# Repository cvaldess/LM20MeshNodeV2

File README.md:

# LM20MeshNode

Pocket [Meshtastic](https://meshtastic.org/) node built around the Nordic **nRF54LM20A**
(Minew ME54BS13 module), with a Minew **MS21SF1** (SX1262) LoRa module, a Minew **ME31GR02**
GNSS receiver and a Nordic **nPM1300** PMIC for a single-cell LiPo battery. It connects to the
phone over Bluetooth LE.

| Front | Back |
|-------|------|
|  |  |

> **Status:** revision 0.2, not yet manufactured or tested. It replaces the Ebyte modules of
> revision 0.1 (E22-900MM22S and E108-GN04S) with Minew modules and adds a backup cell for the
> GNSS. Revision 0.1 is in the [LM20MeshNode](https://github.com/cvaldess/LM20MeshNode)
> repository. A Meshtastic firmware
> variant for revision 0.1 is under review as a draft: see [Meshtastic firmware](#meshtastic-firmware).

## Features

- **MCU:** Minew [nRF54LM20A-ME54BS13](https://en.minewsemi.com/bluetooth-module/nrf54lm20a-me54bs13) (nRF54LM20A, Bluetooth LE with integrated antenna), USB-C to the
  nRF54LM20A USB port, 2×5 1.27 mm Cortex Debug (SWD) header (J201) and debug UART pads.
- **LoRa:** Minew [MS21SF1-SX1262](https://en.minewsemi.com/lora-module/llcc68-sx1262-me21ls1a) (SX1262, up to 22 dBm). The antenna goes to the U.FL
  connector on the module itself. The RF switch inside the module is driven by DIO2, so the
  MCU drives no RXEN/TXEN line. The module supply has its own filter footprint: FB301 (0 Ω,
  or a ferrite bead) and C303.
- **GNSS:** Minew [ME31GR02](https://en.minewsemi.com/gnss-module/me31gr02) (Beken BK166X chip) with U.FL antenna connector (J401). L401 (47 nH)
  feeds an active antenna from the module's VCC_RF output; a passive antenna also works if it
  is not a DC short. The GNSS supply (nPM1300 BUCK1) is off at power-up and is switched by
  firmware.
- **GNSS backup:** a rechargeable Seiko MS621FE coin cell (BT401) on V_BCKP, charged from
  3.3 V through a BAT54WS diode and 1 kΩ. It keeps the RTC and ephemeris data while the board
  is off, for faster fixes.
- **Power:** nPM1300 PMIC with USB-C input and ESD protection, 1S LiPo charger (JST PH 2.0,
  J102), on-board 10 kΩ NTC, 3.3 V main rail (BUCK2), power button (SW101) on SHPHLD, charge
  and error LEDs, and a battery voltage divider to an ADC input.
- **User interface:** 0.91" 128×32 OLED (SSD1306) on the back, three side buttons (UP, OK,
  DOWN), magnetic buzzer and a status LED.
- **Sensors:** Nyfea SHT41-P-NF temperature/humidity sensor (SHT41 compatible), thermally
  isolated by a slot, and an ST LSM6DS3TR-C IMU wired for wake-on-motion (INT1 on P0.02).
- **Expansion:** 4-pin 1 mm I²C connector (J501, Qwiic-style pinout: GND, 3.3 V, SDA, SCL).
- **Board:** 4 layers (signal / GND / 3.3 V / signal), 40 × 85.68 mm, 1.6 mm, M2 mounting
  holes. All SMD parts are on the top side.

## nRF54LM20A pin map

| Function | Pin | Notes |
|----------|-----|-------|
| LoRa SPI (SPIM22): SCK, MOSI, MISO, NSS | P1.17, P1.16, P1.15, P1.18 | |
| LoRa BUSY, DIO1, NRST | P1.19, P1.23, P1.26 | RF switch driven by DIO2 inside the module |
| I²C (TWIM30): SDA, SCL | P0.03, P0.04 | 4.7 kΩ pull-ups |
| GNSS UART (UARTE20): MCU TX → GNSS RXD, GNSS TXD → MCU RX | P1.03, P1.29 | 1 kΩ series resistors; test pads TP402 (GNSS RXD) and TP401 (GNSS TXD) |
| GNSS PPS | P1.04 | |
| GNSS reset | P1.00 | Only through R405 (0 Ω, not fitted). The ME31GR02 reset has an internal pull-up |
| GNSS power enable | P1.05 | To nPM1300 GPIO0 |
| PMIC interrupt | P1.06 | From nPM1300 GPIO1 |
| Battery voltage (divider 2 × 1 MΩ) | P1.30 (AIN2) | |
| Buttons UP, OK, DOWN | P1.27, P1.28, P1.25 | |
| Buzzer (PWM) | P1.09 | |
| Status LED | P2.00 | |
| IMU INT1, INT2 | P0.02, P0.05 | P0 can wake the chip from System OFF |
| Debug UART (UARTE00): TX, RX | P2.02, P2.07 | Test pads |

P1.12 and P1.13 (LoRa TXEN and RXEN in revision 0.1) are free.

I²C devices: nPM1300 `0x6B`, LSM6DS3TR-C `0x6A`, SHT41 `0x44`, OLED `0x3C`.

### Firmware notes

- The nPM1300 starts with the **battery charger disabled**. Firmware must enable charging
  over I²C. The board is designed so that LoRa and Bluetooth work without a PMIC driver.
- The MS21SF1 has a crystal, not a TCXO: do not define a DIO3 TCXO voltage. Use DIO2 as the RF
  switch and define no RXEN/TXEN pins.
- The GNSS rail (BUCK1) must be set to 3.3 V and enabled by firmware.
- The ME31GR02 uses a Beken BK166X chip, which Meshtastic does not detect yet. It talks NMEA at
  115200 bps by default, prints `$POLRS` or `$BKCHIP` at start-up and is configured with
  `$POLCFG…` commands.
- While the GNSS is unpowered or running from the backup cell, no MCU pin connected to it may
  be driven high: put the UART TX pin in input mode with a pull-down. This is why R405 (reset)
  is not fitted.

## Meshtastic firmware

The `lm20meshnode` variant is under review upstream. It was written for **revision 0.1**
(Ebyte modules). All three pull requests are open, and nothing has run on hardware yet:

| Part | Pull request |
|------|--------------|
| Meshtastic variant (draft, on top of the nRF54LM20-DK support in [#12130](https://github.com/meshtastic/firmware/pull/12130)) | [meshtastic/firmware#12354](https://github.com/meshtastic/firmware/pull/12354) |
| Arduino core variant | [andyshinn/nRF54_Arduino#3](https://github.com/andyshinn/nRF54_Arduino/pull/3) |
| Bootloader board | [andyshinn/nRF54_Bootloader#3](https://github.com/andyshinn/nRF54_Bootloader/pull/3) |

Until they are merged, the variant builds from the `feat/lm20meshnode-variant` branch of
[cvaldess/firmware](https://github.com/cvaldess/firmware/tree/feat/lm20meshnode-variant) with
`pio run -e lm20meshnode`. The core and the bootloader come from forks (the core at a pinned commit,
the bootloader at the tag `v0.5.0-lm20meshnode.1`).

What the variant does on revision 0.1:

- **nPM1300**, set up over I²C at boot: BUCK1 (GNSS rail) at 3.3 V, switched by the PMIC's GPIO0,
  which the GPS code drives from P1.05; battery charger on at 200 mA (`NPM1300_CHARGE_CURRENT_MA`),
  4.20 V (4.00 V in the warm region), with the on-board 10 kΩ NTC; USB input limit 500 mA. BUCK2,
  the 3.3 V main rail, is left on its VSET2 setting. After USB is unplugged and plugged in again,
  the PMIC goes back to its 100 mA startup input limit until the next boot.
- **LoRa** with RXEN from the MCU and TXEN from DIO2, no TCXO. **GNSS** on `Serial1` at 38400 bps.
- **Buttons:** UP, DOWN and OK navigate the screen (up/down input driver). **OLED** at 128×32,
  **buzzer**, **status LED**, **battery** level from AIN2, and the SHT41 and LSM6DS3TR-C drivers.
- **USB-C:** console and Meshtastic API over USB CDC; firmware updates over USB (serial DFU or a
  UF2 drive) or over Bluetooth.
- **Bootloader** (64 KB, application at `0x10000`): hold **OK** at reset for USB DFU (UF2 drive
  `LM20MN-BOOT`), **OK + DOWN** for Bluetooth OTA. The status LED shows the bootloader state.

Revision 0.2 needs these changes in the variant: DIO2 as the RF switch and no RXEN pin (LoRa),
a detection probe for the Beken GNSS at 115200 bps, the GNSS UART TX pin left as an input with a
pull-down while the GNSS is off, and no GNSS reset pin.

Not tested yet, besides the board itself: the nPM1300 setup, GPS on the nRF54 platform (no other
nRF54 variant uses it so far), the 128×32 screen layout and the battery reading through the
2 × 1 MΩ divider.

## Manufacturing

The [`fab/pcbway/`](fab/pcbway/) folder contains:

- `nrflm20-meshnode_rev0.2_pcbway.zip`: Gerber files (4 copper layers, masks, top paste,
  silkscreen, outline), Excellon drill files (PTH and NPTH) and an IPC-D-356 netlist.
- `gerber/`: the same files unzipped, plus drill maps and the drill report.
- `nrflm20-meshnode-BOM-PCBWay.csv`: bill of materials (40 lines, 70 parts) with manufacturer part
  numbers and LCSC codes. A few passives are generic parts, listed by specification.
- `nrflm20-meshnode-CPL-PCBWay.csv`: component placement (centroid) file in millimetres, in the
  same coordinate system as the Gerber files. The OLED (DS501) is the only part on the bottom side.
- `pedido_pcbway.txt`: order settings and pre-production checks (in Spanish).

Not fitted (DNP) and left out of the BOM and placement files: R404, R405. Mounting holes and
test points are not parts and are left out too.

**BT401 is soldered by hand.** The MS621FE-FL11E coin cell must not go through reflow (Seiko:
soldering iron, 5 s maximum, cell below 85 °C), so it is left out of the BOM and placement
files. Its pads do get paste in the stencil, which tins them during reflow; solder the cell
last.

Board: 4 layers, 1.6 mm, 1 oz copper, ENIG recommended, minimum track/space 0.2 mm, minimum
drill 0.3 mm. Stencil: top side only, 0.10 mm, needed by the 0.5 mm pitch parts. Minew
recommends thicker paste on its modules (0.13–0.2 mm); with 0.10 mm, check the castellated
pads after reflow and touch them up with a soldering iron if needed. The standard PCBWay
4-layer stackup is fine; impedance control is not needed (the only RF track on the board, from
J401 to the GNSS module, is 3.9 mm long).

The files are generated from the saved board with `docs/gen/fab_pcbway.py` (Gerber, drill,
IPC-D-356) and `docs/gen/bom_cpl_pcbway.py` (BOM and placement), using KiCad's Python.

## Design files

- [KiCad 10](https://www.kicad.org/) project: `nrflm20-meshnode.kicad_pro`. The root schematic
  has five sheets: power, MCU, LoRa, GNSS and interface.
- `libs/`: project symbols, footprints and 3D models. The MS21SF1 and ME31GR02 footprints were
  converted from Minew's design files (`docs/gen/huellas_minew.py`). The ME54BS13 3D model was
  drawn from its datasheet (`docs/gen/modelo3d_me54bs13.py`).
- **3D models of the MS21SF1 and ME31GR02 are not included yet**: they are Minew's files and are
  waiting for Minew's permission to publish them. The footprints already point to
  `libs/meshnode.3dshapes/MS21SF1_PCB_V1.0.step` and `libs/meshnode.3dshapes/GNSS_MODULE_1010.step`,
  so a clone of this repository renders the board without those two modules.
- `docs/`: block diagram and schematic drafts (SVG). `docs/gen/` has the Python scripts used
  during the design.
- `lista_compra.txt`: shopping list (in Spanish).

Some footprints and 3D models come from [easyeda2kicad](https://github.com/uPesy/easyeda2kicad.py)
(`${EASYEDA2KICAD}`). The footprints are stored in the board file, but their 3D models are
not included in this repository.

## Credits

- **Designed by:** solutions@cvaldess.com
- **Made with:** [Claude Code](https://claude.com/claude-code), [KiCad](https://www.kicad.org/)
  and [Konnect-EDA](https://github.com/Orchis-ai-LLC/Konnect-EDA)
- **Sponsors:** [PCBWay](https://www.pcbway.com/) and [MinewSemi](https://www.minewsemi.com/)
  (ME54BS13, MS21SF1 and ME31GR02 modules)

## License

Copyright © 2026 CValdesS.

This source describes Open Hardware and is licensed under the CERN-OHL-S v2
([LICENSE](LICENSE)). You may redistribute and modify this source and make products using it
under the terms of the CERN-OHL-S v2. This source is distributed WITHOUT ANY EXPRESS OR IMPLIED
WARRANTY, INCLUDING OF MERCHANTABILITY, SATISFACTORY QUALITY AND FITNESS FOR A PARTICULAR
PURPOSE. Please see the CERN-OHL-S v2 for applicable conditions.

Source location: https://github.com/cvaldess/LM20MeshNodeV2

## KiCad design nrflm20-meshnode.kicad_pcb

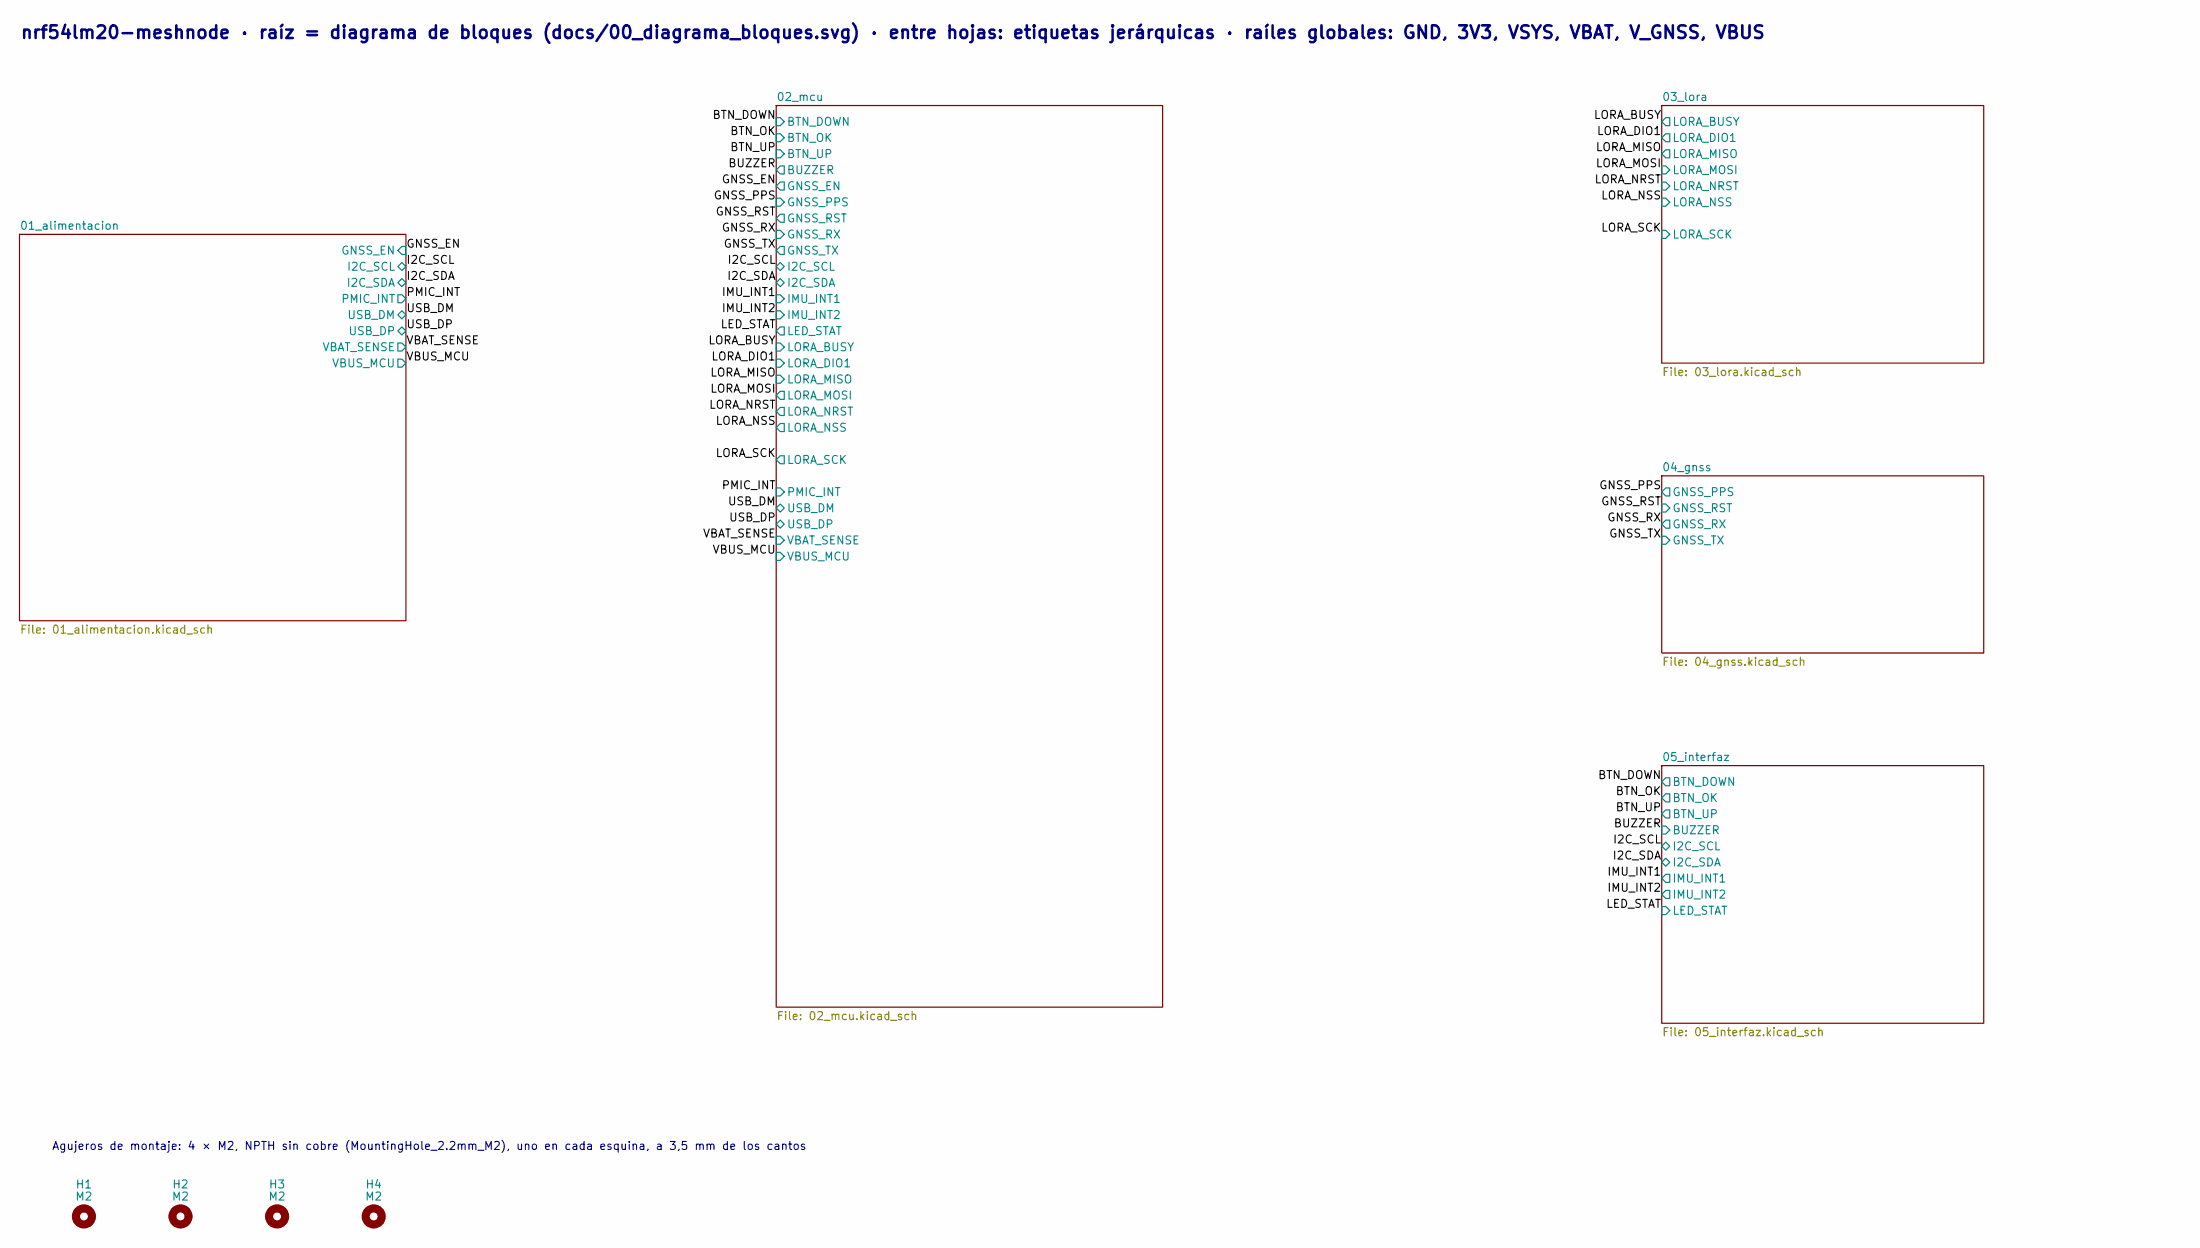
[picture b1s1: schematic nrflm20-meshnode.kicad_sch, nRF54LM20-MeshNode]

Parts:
H1, H2, H3, H4: M2; MountingHole_2.2mm_M2

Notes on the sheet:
nrf54lm20-meshnode · raíz = diagrama de bloques (docs/00_diagrama_bloques.svg) · entre hojas: etiquetas jerárquicas · raíles globales: GND, 3V3, VSYS, VBAT, V_GNSS, VBUS
Agujeros de montaje: 4 × M2, NPTH sin cobre (MountingHole_2.2mm_M2), uno en cada esquina, a 3,5 mm de los cantos

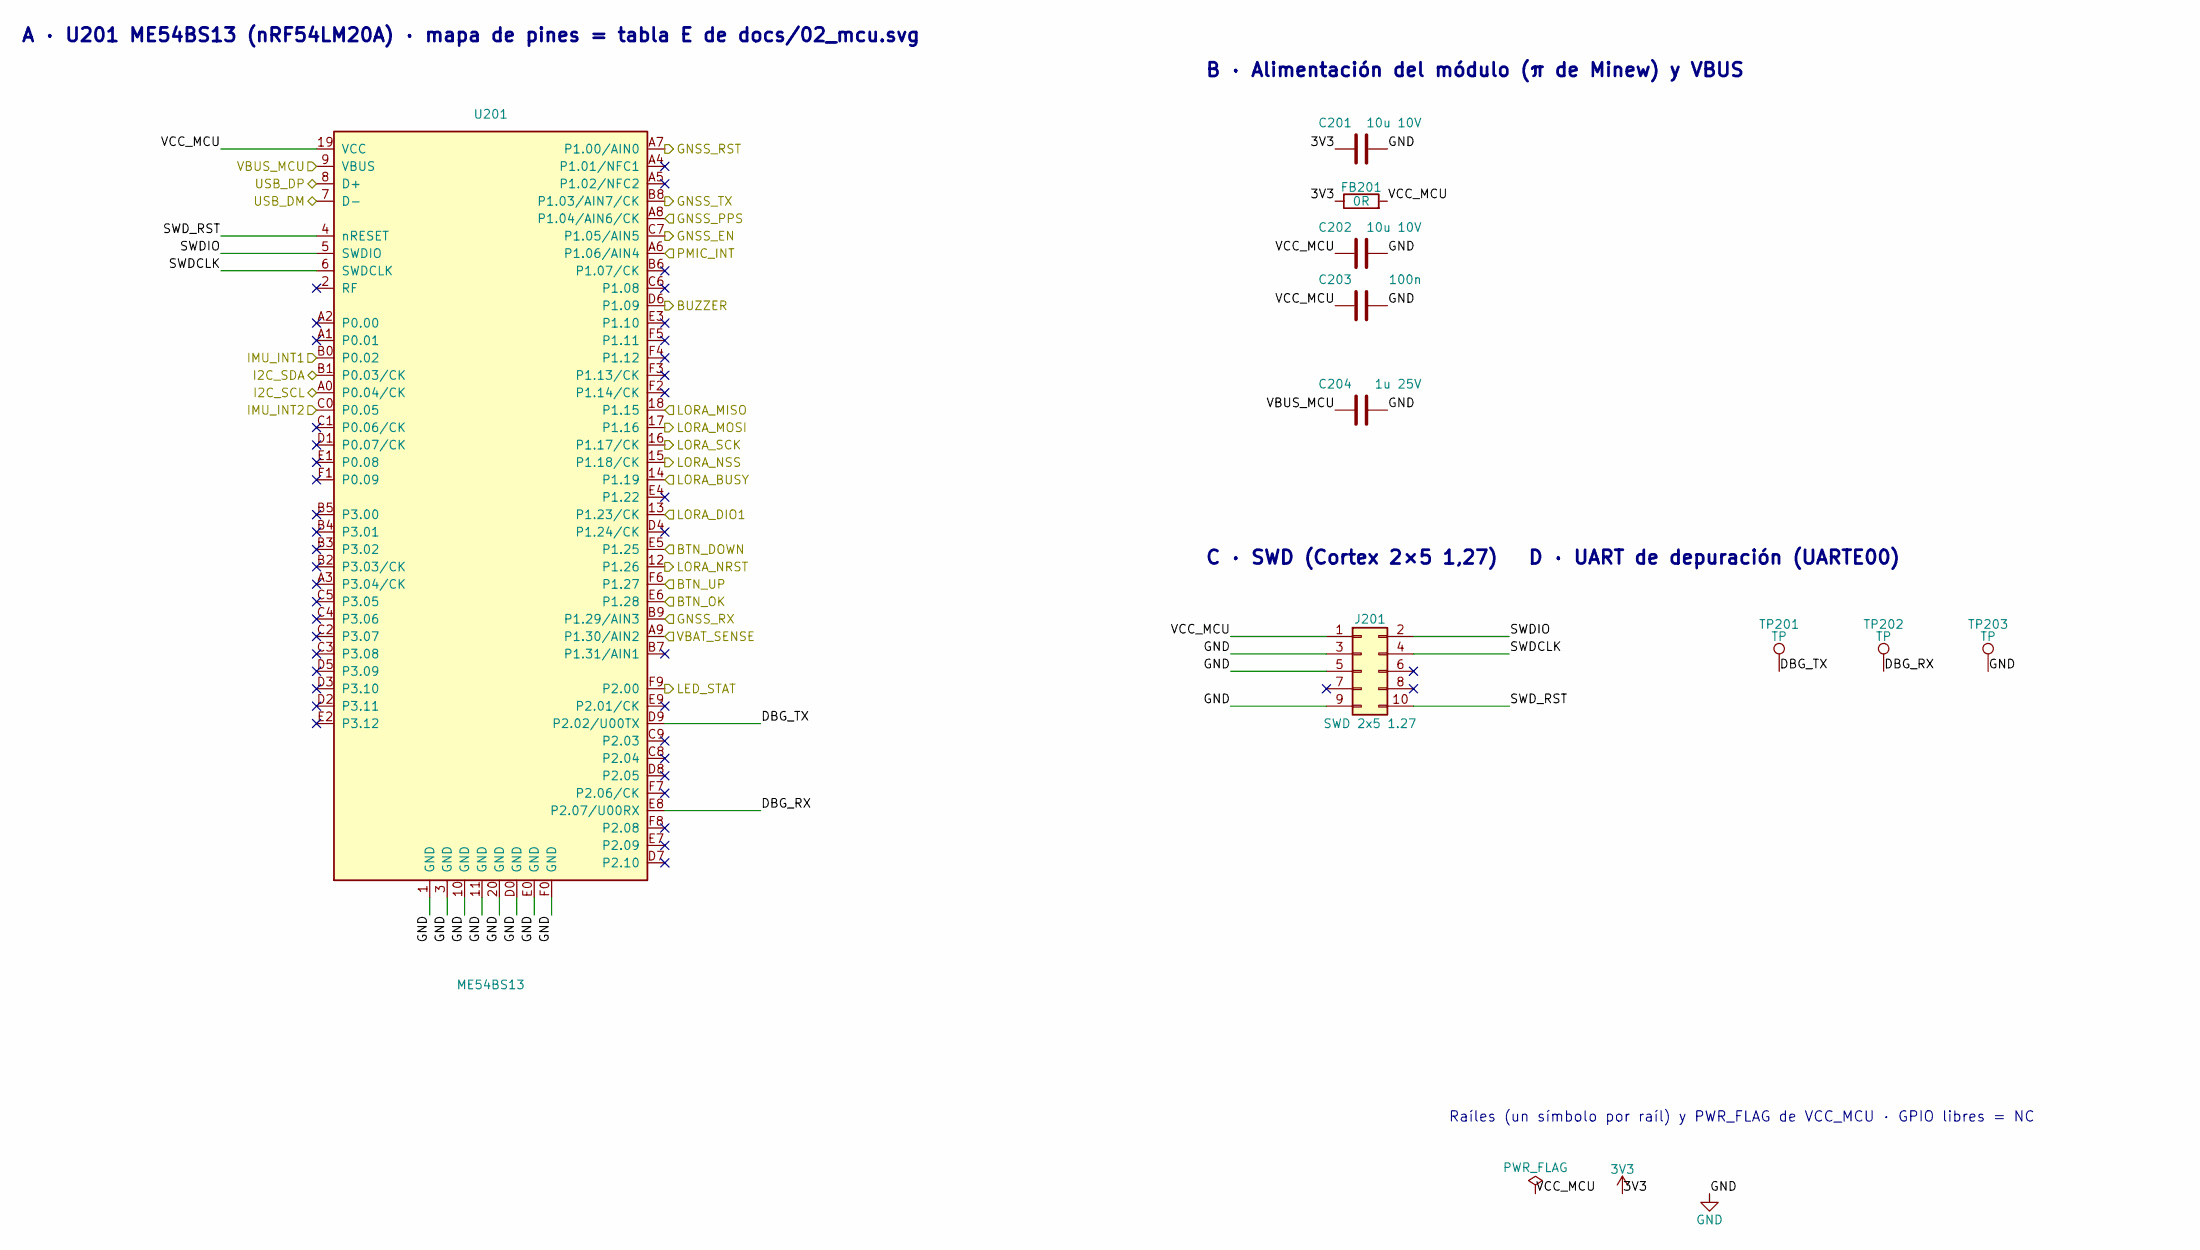
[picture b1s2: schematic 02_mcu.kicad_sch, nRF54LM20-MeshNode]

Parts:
C201, C202: 10u 10V; C_0603_1608Metric
C203: 100n; C_0402_1005Metric; MPN CL05B104KO5NNNC; LCSC Part C1525
C204: 1u 25V; C_0402_1005Metric; MPN CL05A105KA5NQNC; LCSC Part C52923
FB201: 0R; R_0603_1608Metric
J201: SWD 2x5 1.27; PinHeader_2x05_P1.27mm_Vertical_SMD; MPN HX PZ1.27-2x5P TP; LCSC Part C41376037
TP201, TP202, TP203: TP; TestPoint_Pad_D1.0mm
U201: ME54BS13; MPN ME54BS13 (nRF54LM20A)

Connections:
3V3: C201.1, FB201.1; also elsewhere on the board
/02_mcu/DBG_RX: TP202.1 (1_1), U201.E8 (P2.07/U00RX)
/02_mcu/DBG_TX: TP201.1 (1_1), U201.D9 (P2.02/U00TX)
/02_mcu/SWDCLK: J201.4, U201.6 (SWDCLK)
/02_mcu/SWDIO: J201.2, U201.5 (SWDIO)
/02_mcu/SWD_RST: J201.10, U201.4 (nRESET)
/02_mcu/VCC_MCU: C202.1, C203.1, FB201.2, J201.1, U201.19 (VCC)
/BTN_DOWN: U201.E5 (P1.25); also elsewhere on the board
/BTN_OK: U201.E6 (P1.28); also elsewhere on the board
/BTN_UP: U201.F6 (P1.27); also elsewhere on the board
/BUZZER: U201.D6 (P1.09); also elsewhere on the board
/GNSS_EN: U201.C7 (P1.05/AIN5); also elsewhere on the board
/GNSS_PPS: U201.A8 (P1.04/AIN6/CK); also elsewhere on the board
/GNSS_RST: U201.A7 (P1.00/AIN0); also elsewhere on the board
/GNSS_RX: U201.B9 (P1.29/AIN3); also elsewhere on the board
/GNSS_TX: U201.B8 (P1.03/AIN7/CK); also elsewhere on the board
/I2C_SCL: U201.A0 (P0.04/CK); also elsewhere on the board
/I2C_SDA: U201.B1 (P0.03/CK); also elsewhere on the board
/IMU_INT1: U201.B0 (P0.02); also elsewhere on the board
/IMU_INT2: U201.C0 (P0.05); also elsewhere on the board
/LED_STAT: U201.F9 (P2.00); also elsewhere on the board
/LORA_BUSY: U201.14 (P1.19); also elsewhere on the board
/LORA_DIO1: U201.13 (P1.23/CK); also elsewhere on the board
/LORA_MISO: U201.18 (P1.15); also elsewhere on the board
/LORA_MOSI: U201.17 (P1.16); also elsewhere on the board
/LORA_NRST: U201.12 (P1.26); also elsewhere on the board
/LORA_NSS: U201.15 (P1.18/CK); also elsewhere on the board
/LORA_SCK: U201.16 (P1.17/CK); also elsewhere on the board
/PMIC_INT: U201.A6 (P1.06/AIN4); also elsewhere on the board
/USB_DM: U201.7 (D-); also elsewhere on the board
/USB_DP: U201.8 (D+); also elsewhere on the board
/VBAT_SENSE: U201.A9 (P1.30/AIN2); also elsewhere on the board
/VBUS_MCU: C204.1, U201.9 (VBUS); also elsewhere on the board
GND: C201.2, C202.2, C203.2, C204.2, J201.3, J201.5, J201.9, TP203.1 (1_1), U201.1 (GND), U201.3 (GND), U201.10 (GND), U201.11 (GND), U201.20 (GND), U201.D0 (GND), U201.E0 (GND), U201.F0 (GND); also elsewhere on the board

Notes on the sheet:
B · Alimentación del módulo (π de Minew) y VBUS
A · U201 ME54BS13 (nRF54LM20A) · mapa de pines = tabla E de docs/02_mcu.svg
C · SWD (Cortex 2×5 1,27) D · UART de depuración (UARTE00)
Raíles (un símbolo por raíl) y PWR_FLAG de VCC_MCU · GPIO libres = NC

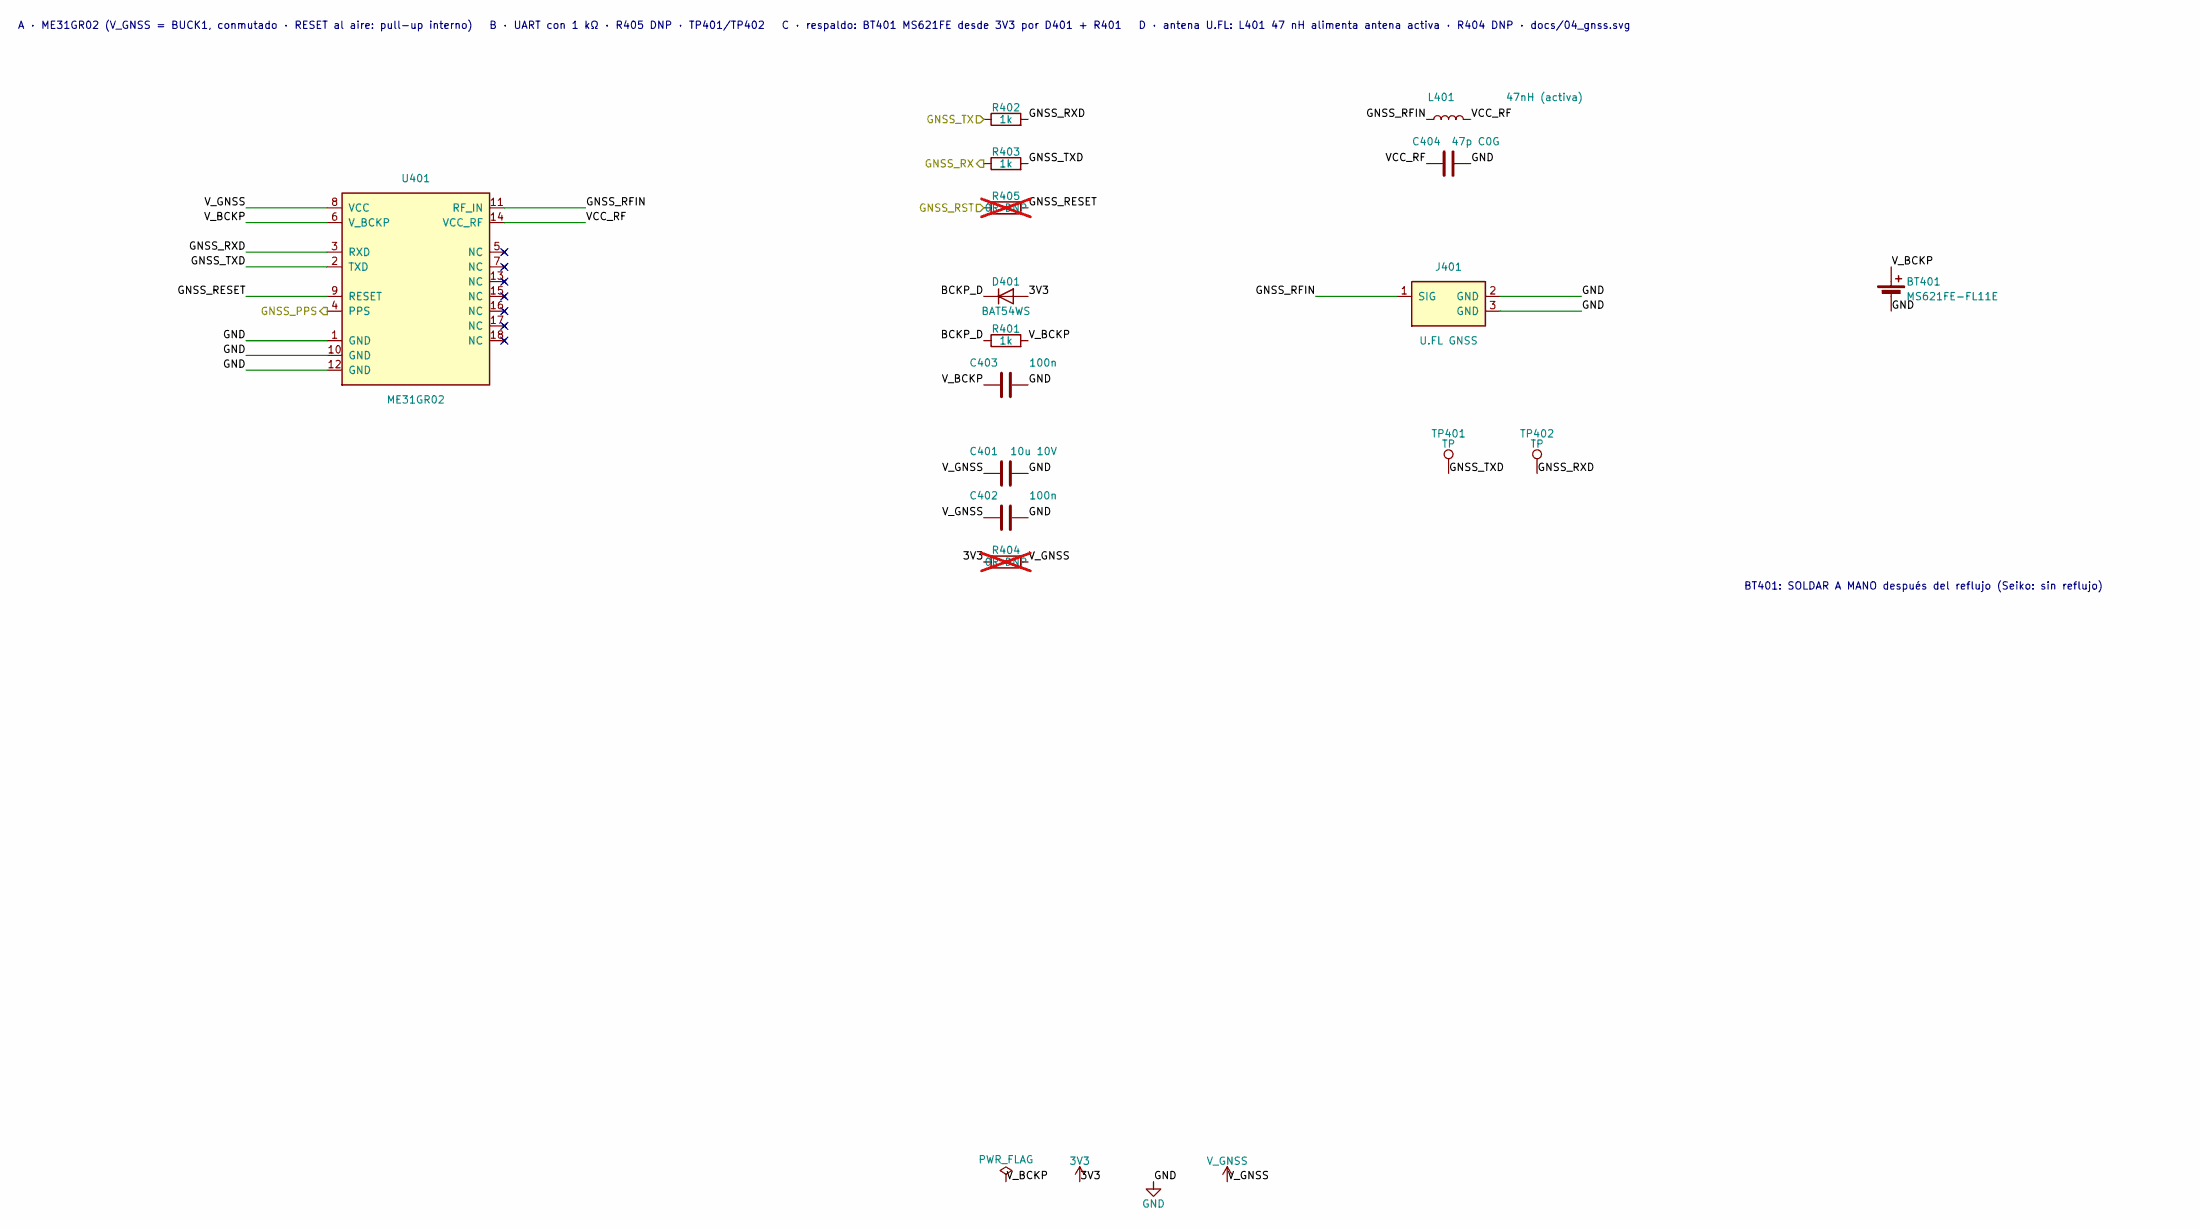
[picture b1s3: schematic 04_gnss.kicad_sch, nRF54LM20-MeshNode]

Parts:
BT401: MS621FE-FL11E; BatteryHolder_Seiko_MS621F; MPN MS621FE-FL11E
C401: 10u 10V; C_0603_1608Metric
C402, C403: 100n; C_0402_1005Metric; MPN CL05B104KO5NNNC; LCSC Part C1525
C404: 47p C0G; C_0402_1005Metric; MPN 0402CG470F500NT; LCSC Part C42563629
D401: BAT54WS; D_SOD-323; MPN BAT54WS-7-F; LCSC Part C124205
J401: U.FL GNSS; IPEX-SMD_BWIPX-1-001E; MPN BWU.FL-IPEX1; LCSC Part C5137195
L401: 47nH (activa); L_0402_1005Metric; MPN LQW15AN47NJ00D; LCSC Part C192855
R401, R402, R403: 1k; R_0402_1005Metric; MPN 0402WGF1001TCE; LCSC Part C11702
R404, R405: 0R DNP; R_0402_1005Metric; MPN RC0402FR-070RL; LCSC Part C106231; not fitted
TP401, TP402: TP; TestPoint_Pad_D1.0mm
U401: ME31GR02; MPN ME31GR02

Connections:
3V3: D401.2 (A), R404.1; also elsewhere on the board
/04_gnss/BCKP_D: D401.1 (K), R401.1
/04_gnss/GNSS_RESET: R405.2, U401.9 (RESET)
/04_gnss/GNSS_RFIN: J401.1 (SIG), L401.1, U401.11 (RF_IN)
/04_gnss/GNSS_RXD: R402.2, TP402.1 (1_1), U401.3 (RXD)
/04_gnss/GNSS_TXD: R403.2, TP401.1 (1_1), U401.2 (TXD)
/04_gnss/VCC_RF: C404.1, L401.2, U401.14 (VCC_RF)
/04_gnss/V_BCKP: BT401.1 (+), C403.1, R401.2, U401.6 (V_BCKP)
/GNSS_PPS: U401.4 (PPS); also elsewhere on the board
/GNSS_RST: R405.1; also elsewhere on the board
/GNSS_RX: R403.1; also elsewhere on the board
/GNSS_TX: R402.1; also elsewhere on the board
GND: BT401.2 (-), C401.2, C402.2, C403.2, C404.2, J401.2 (GND), J401.3 (GND), U401.1 (GND), U401.10 (GND), U401.12 (GND); also elsewhere on the board
V_GNSS: C401.1, C402.1, R404.2, U401.8 (VCC); also elsewhere on the board

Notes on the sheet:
A · ME31GR02 (V_GNSS = BUCK1, conmutado · RESET al aire: pull-up interno) B · UART con 1 kΩ · R405 DNP · TP401/TP402 C · respaldo: BT401 MS621FE desde 3V3 por D401 + R401 D · antena U.FL: L401 47 nH alimenta antena activa · R404 DNP · docs/04_gnss.svg
BT401: SOLDAR A MANO después del reflujo (Seiko: sin reflujo)

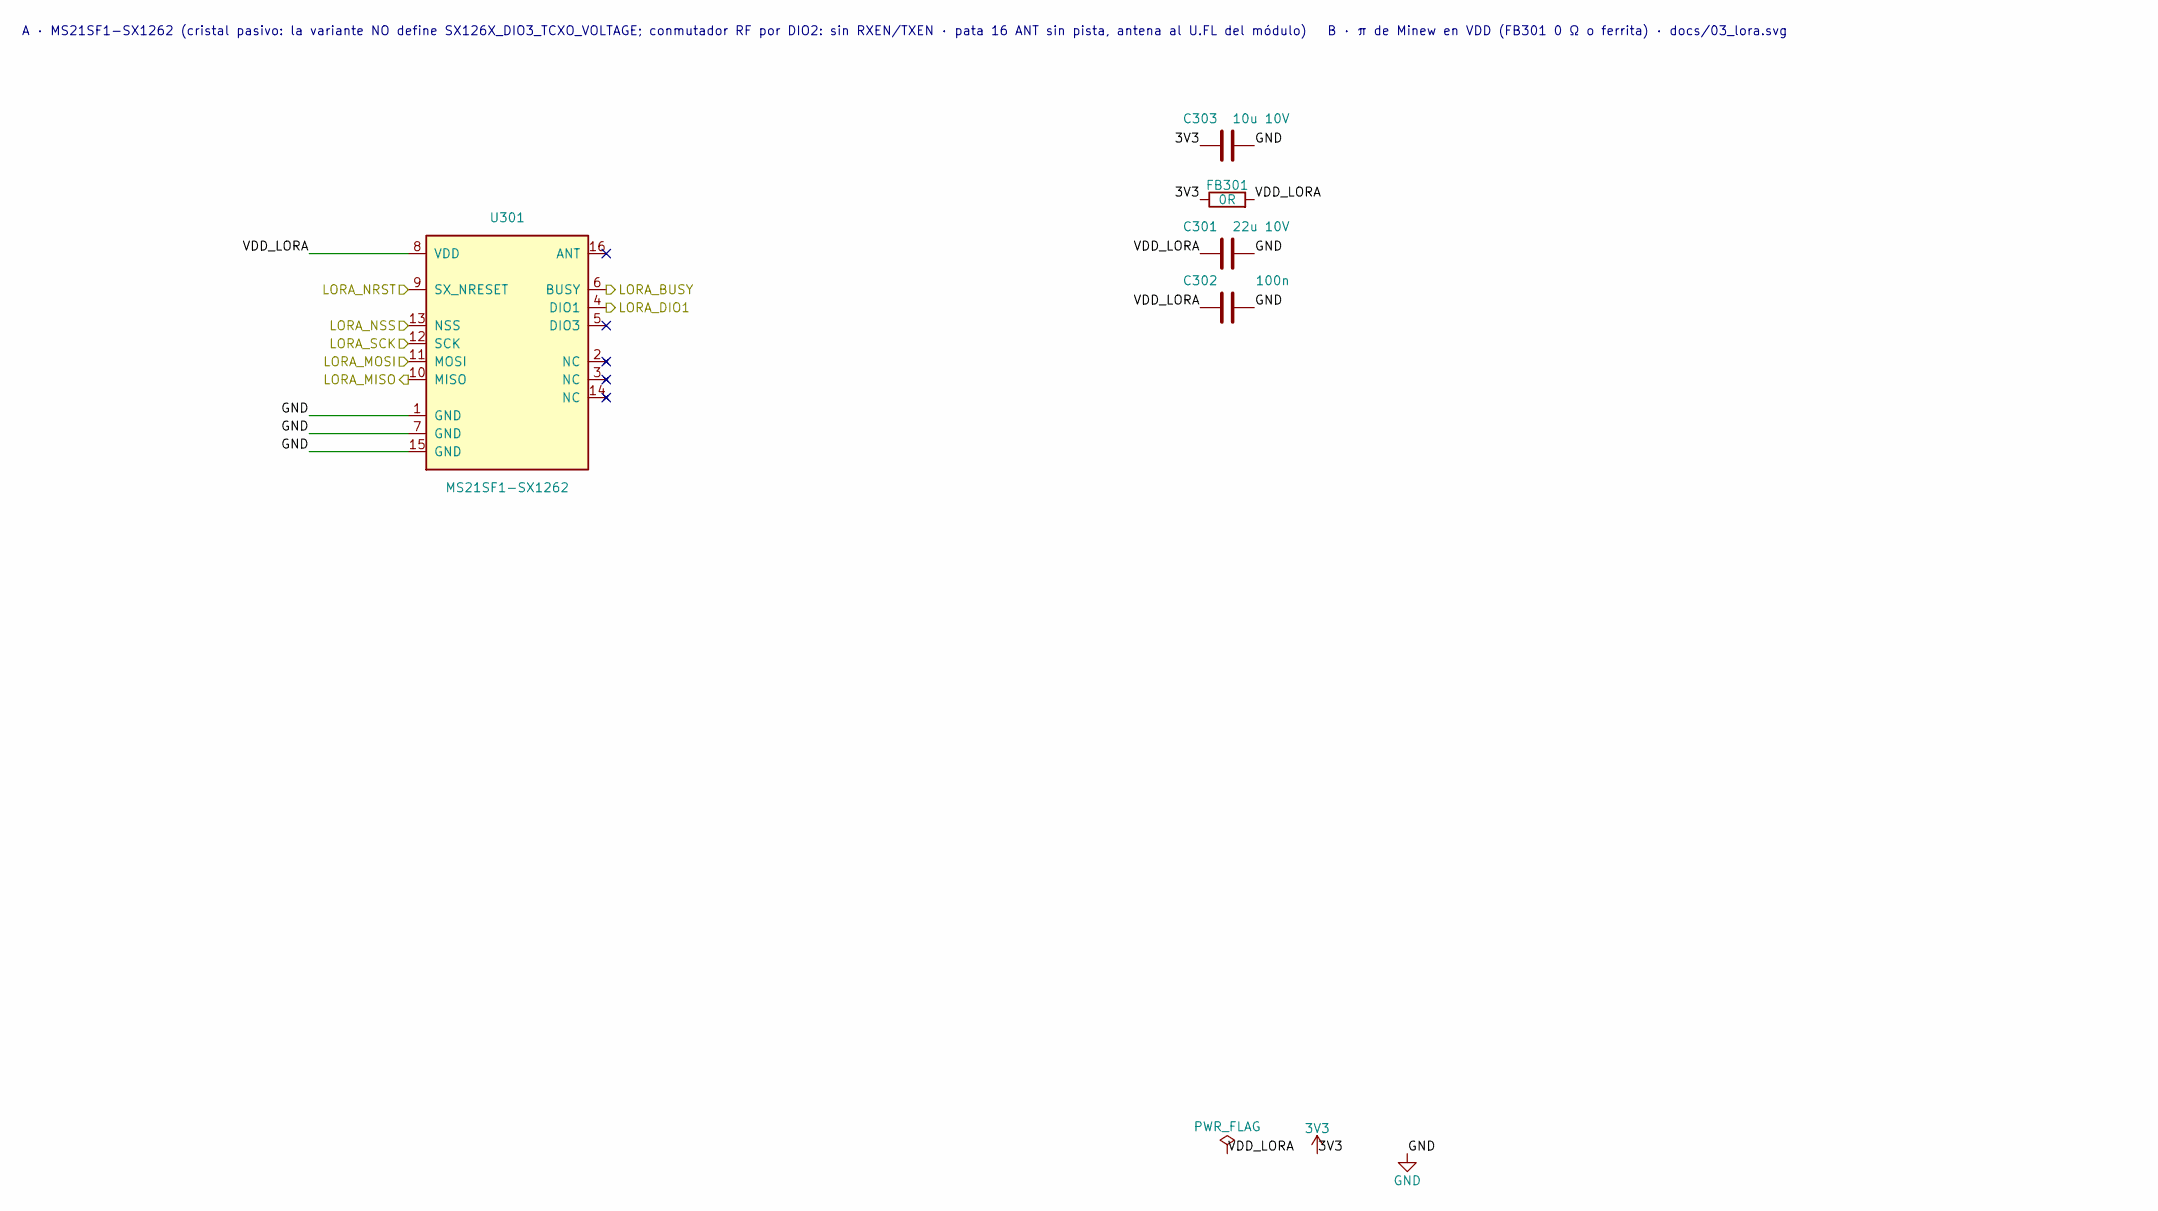
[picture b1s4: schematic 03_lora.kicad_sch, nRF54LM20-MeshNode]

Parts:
C301: 22u 10V; C_0603_1608Metric
C302: 100n; C_0402_1005Metric; MPN CL05B104KO5NNNC; LCSC Part C1525
C303: 10u 10V; C_0603_1608Metric
FB301: 0R; R_0603_1608Metric
U301: MS21SF1-SX1262; MS21SF1; MPN MS21SF1-SX1262

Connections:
3V3: C303.1, FB301.1; also elsewhere on the board
/03_lora/VDD_LORA: C301.1, C302.1, FB301.2, U301.8 (VDD)
/LORA_BUSY: U301.6 (BUSY); also elsewhere on the board
/LORA_DIO1: U301.4 (DIO1); also elsewhere on the board
/LORA_MISO: U301.10 (MISO); also elsewhere on the board
/LORA_MOSI: U301.11 (MOSI); also elsewhere on the board
/LORA_NRST: U301.9 (SX_NRESET); also elsewhere on the board
/LORA_NSS: U301.13 (NSS); also elsewhere on the board
/LORA_SCK: U301.12 (SCK); also elsewhere on the board
GND: C301.2, C302.2, C303.2, U301.1 (GND), U301.7 (GND), U301.15 (GND); also elsewhere on the board

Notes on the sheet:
A · MS21SF1-SX1262 (cristal pasivo: la variante NO define SX126X_DIO3_TCXO_VOLTAGE; conmutador RF por DIO2: sin RXEN/TXEN · pata 16 ANT sin pista, antena al U.FL del módulo) B · π de Minew en VDD (FB301 0 Ω o ferrita) · docs/03_lora.svg

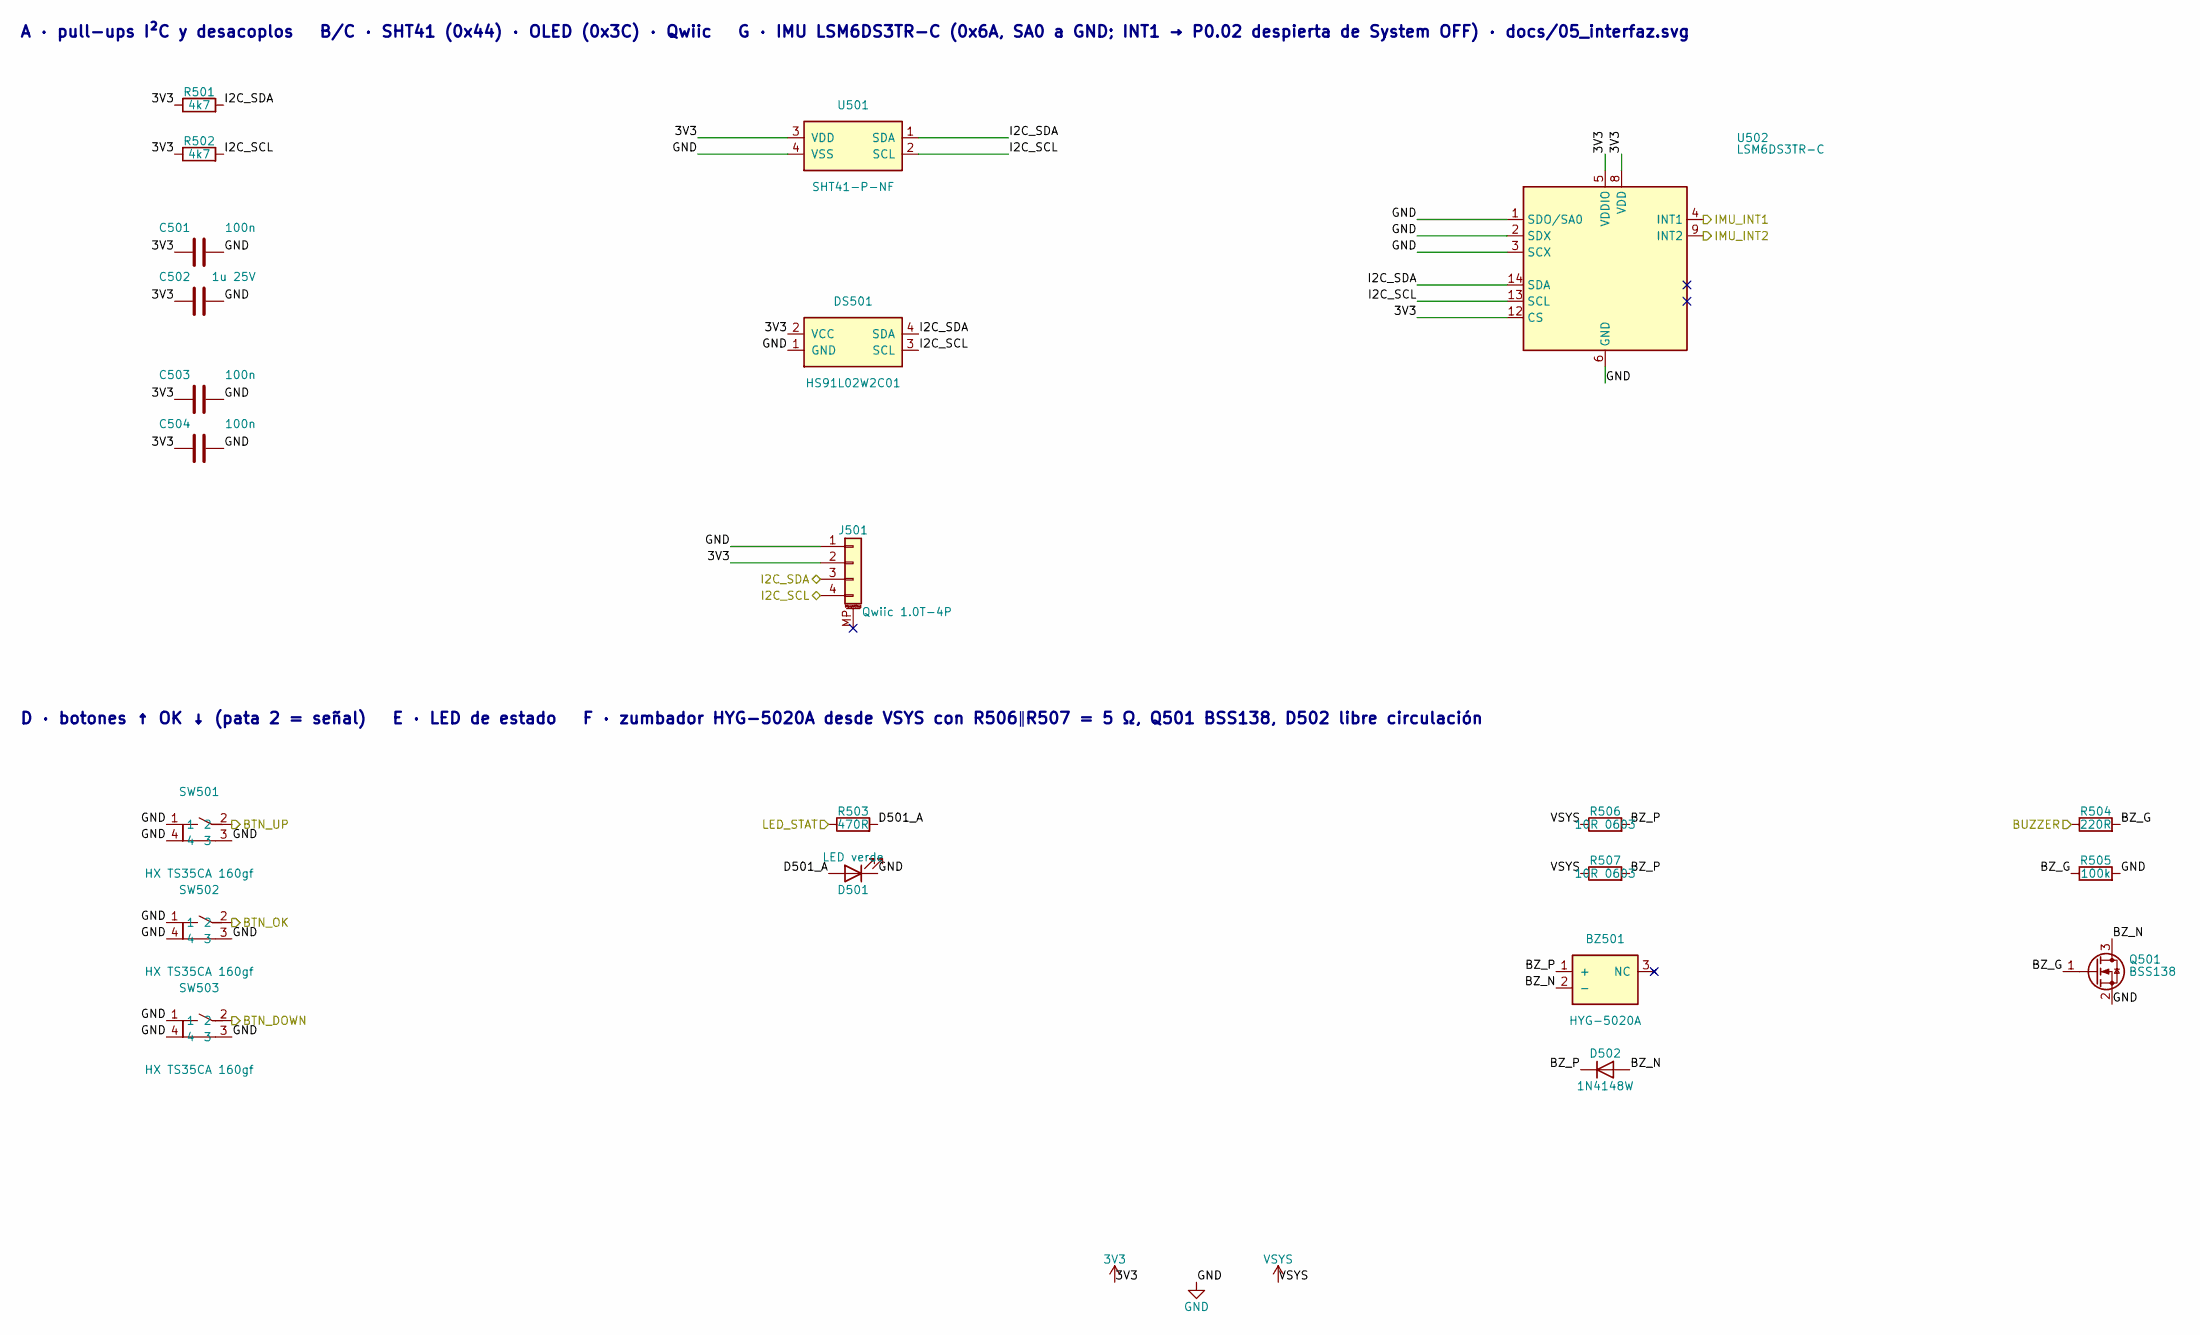
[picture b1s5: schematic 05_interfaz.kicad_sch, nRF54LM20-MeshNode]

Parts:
BZ501: HYG-5020A; BUZ-SMD_3P-L5.0-W5.0-P3.50-BL; MPN HYG-5020A; LCSC Part C7544810
C501, C503, C504: 100n; C_0402_1005Metric; MPN CL05B104KO5NNNC; LCSC Part C1525
C502: 1u 25V; C_0402_1005Metric; MPN CL05A105KA5NQNC; LCSC Part C52923
D501: LED verde; LED_0603_1608Metric; MPN XL-1608UGC-06A; LCSC Part C7371903
D502: 1N4148W; D_SOD-123; MPN 1N4148W; LCSC Part C917030
DS501: HS91L02W2C01; OLED-TH_L38.0-W12.0_HS91L02W2C01; MPN HS91L02W2C01; LCSC Part C5248081
J501: Qwiic 1.0T-4P; BOOMELE_1.0T-4P_1x04-1MP_P1.00mm_Horizontal; MPN 1.0T-4P; LCSC Part C970137
Q501: BSS138; SOT-23; MPN BSS138; LCSC Part C27140738
R501, R502: 4k7; R_0402_1005Metric; MPN RC0402FR-074K7L; LCSC Part C105871
R503: 470R; R_0402_1005Metric; MPN 0402WGF4700TCE; LCSC Part C25117
R504: 220R; R_0402_1005Metric; MPN 0402WGF2200TCE; LCSC Part C25091
R505: 100k; R_0402_1005Metric; MPN RC0402FR-07100KL; LCSC Part C60491
R506, R507: 10R 0603; R_0603_1608Metric
SW501, SW502, SW503: HX TS35CA 160gf; KEY-SMD_HX-TS35CA-250GF; MPN HX TS35CA 160gf; LCSC Part C25168837
U501: SHT41-P-NF; DFN-4_L1.5-W1.5-SHT41-AD1B-R2; MPN SHT41-P-NF; LCSC Part C55108905
U502: LSM6DS3TR-C; LGA-14_L3.0-W2.5-P0.50-TL; MPN LSM6DS3TR-C; LCSC Part C967633

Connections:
3V3: C501.1, C502.1, C503.1, C504.1, DS501.2 (VCC), J501.2, R501.1, R502.1, U501.3 (VDD), U502.5 (VDDIO), U502.8 (VDD), U502.12 (CS); also elsewhere on the board
/05_interfaz/BZ_G: Q501.1 (G), R504.2, R505.1
/05_interfaz/BZ_N: BZ501.2 (-), D502.2 (A), Q501.3 (D)
/05_interfaz/BZ_P: BZ501.1 (+), D502.1 (K), R506.2, R507.2
/05_interfaz/D501_A: D501.2 (A), R503.2
/BTN_DOWN: SW503.2; also elsewhere on the board
/BTN_OK: SW502.2; also elsewhere on the board
/BTN_UP: SW501.2; also elsewhere on the board
/BUZZER: R504.1; also elsewhere on the board
/I2C_SCL: DS501.3 (SCL), J501.4, R502.2, U501.2 (SCL), U502.13 (SCL); also elsewhere on the board
/I2C_SDA: DS501.4 (SDA), J501.3, R501.2, U501.1 (SDA), U502.14 (SDA); also elsewhere on the board
/IMU_INT1: U502.4 (INT1); also elsewhere on the board
/IMU_INT2: U502.9 (INT2); also elsewhere on the board
/LED_STAT: R503.1; also elsewhere on the board
GND: C501.2, C502.2, C503.2, C504.2, D501.1 (K), DS501.1 (GND), J501.1, Q501.2 (S), R505.2, SW501.1, SW501.3, SW501.4, SW502.1, SW502.3, SW502.4, SW503.1, SW503.3, SW503.4, U501.4 (VSS), U502.1 (SDO/SA0), U502.2 (SDX), U502.3 (SCX), U502.6 (GND), U502.7 (GND); also elsewhere on the board
VSYS: R506.1, R507.1; also elsewhere on the board

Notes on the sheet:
A · pull-ups I²C y desacoplos B/C · SHT41 (0x44) · OLED (0x3C) · Qwiic G · IMU LSM6DS3TR-C (0x6A, SA0 a GND; INT1 → P0.02 despierta de System OFF) · docs/05_interfaz.svg
D · botones ↑ OK ↓ (pata 2 = señal) E · LED de estado F · zumbador HYG-5020A desde VSYS con R506∥R507 = 5 Ω, Q501 BSS138, D502 libre circulación
